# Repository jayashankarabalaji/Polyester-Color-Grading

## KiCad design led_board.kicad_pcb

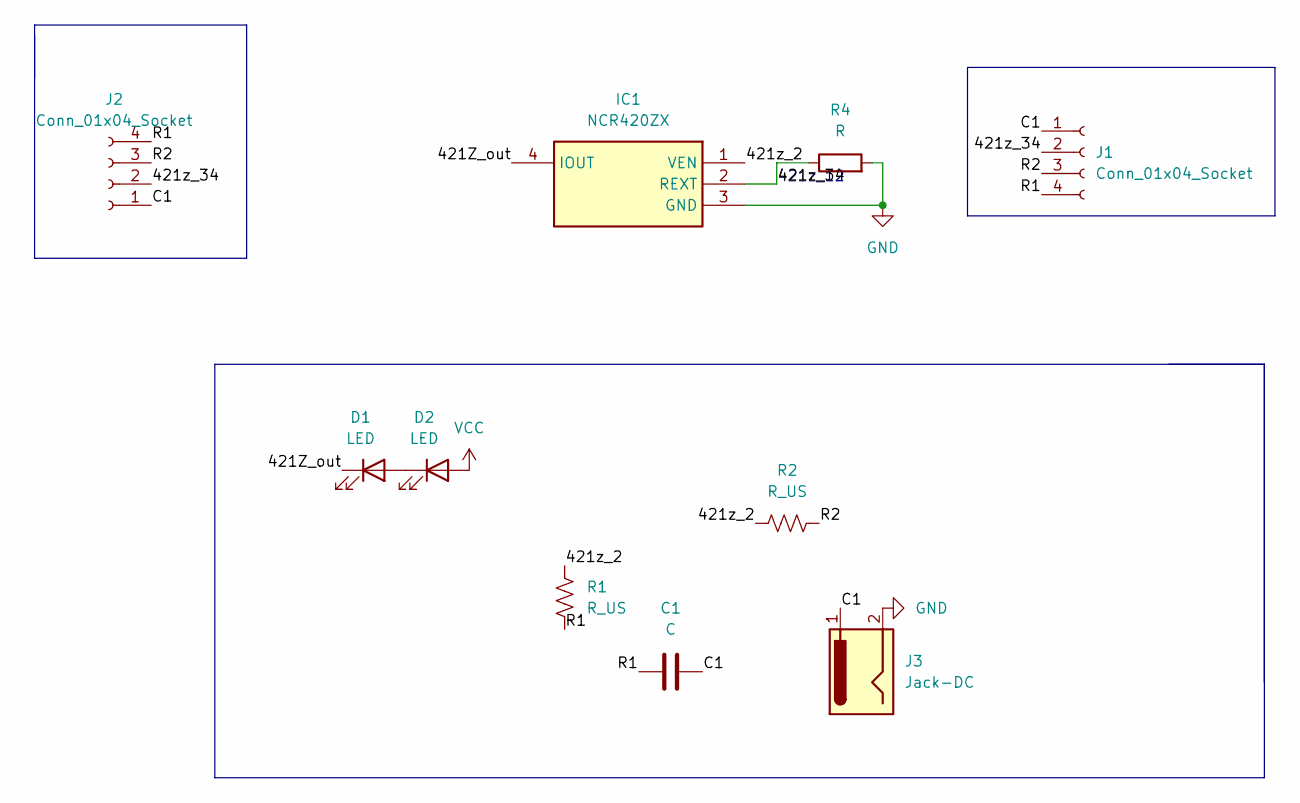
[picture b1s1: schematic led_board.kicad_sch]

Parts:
C1: C; C_0603_1608Metric
D1, D2: LED; LED_0201_0603Metric
IC1: NCR420ZX; SOT230P700X180-4N; Mouser Part Number 771-NCR420ZX
J1, J2: Conn_01x04_Socket; PinSocket_1x04_P1.00mm_Vertical
J3: Jack-DC; PinHeader_1x02_P1.00mm_Horizontal
R1, R2: R_US; R_0603_1608Metric
R4: R; LED_0201_0603Metric

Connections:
/421Z_out: D1.1 (K), IC1.4 (IOUT)
/421z_2: IC1.1 (VEN), R1.1, R2.2
/421z_34: IC1.2 (REXT), J1.2, J2.2, R4.1
/C1: C1.2, J1.1, J2.1, J3.1
/R1: C1.1, J1.4, J2.4, R1.2
/R2: J1.3, J2.3, R2.1
GND: IC1.3 (GND), J3.2, R4.2
unnamed: D1.2 (A), D2.1 (K)
VCC: D2.2 (A)

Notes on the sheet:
421z_12

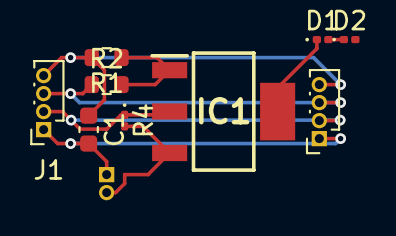
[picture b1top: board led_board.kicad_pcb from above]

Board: 2 copper layers, 10 parts (1 on the bottom side), 8 nets.

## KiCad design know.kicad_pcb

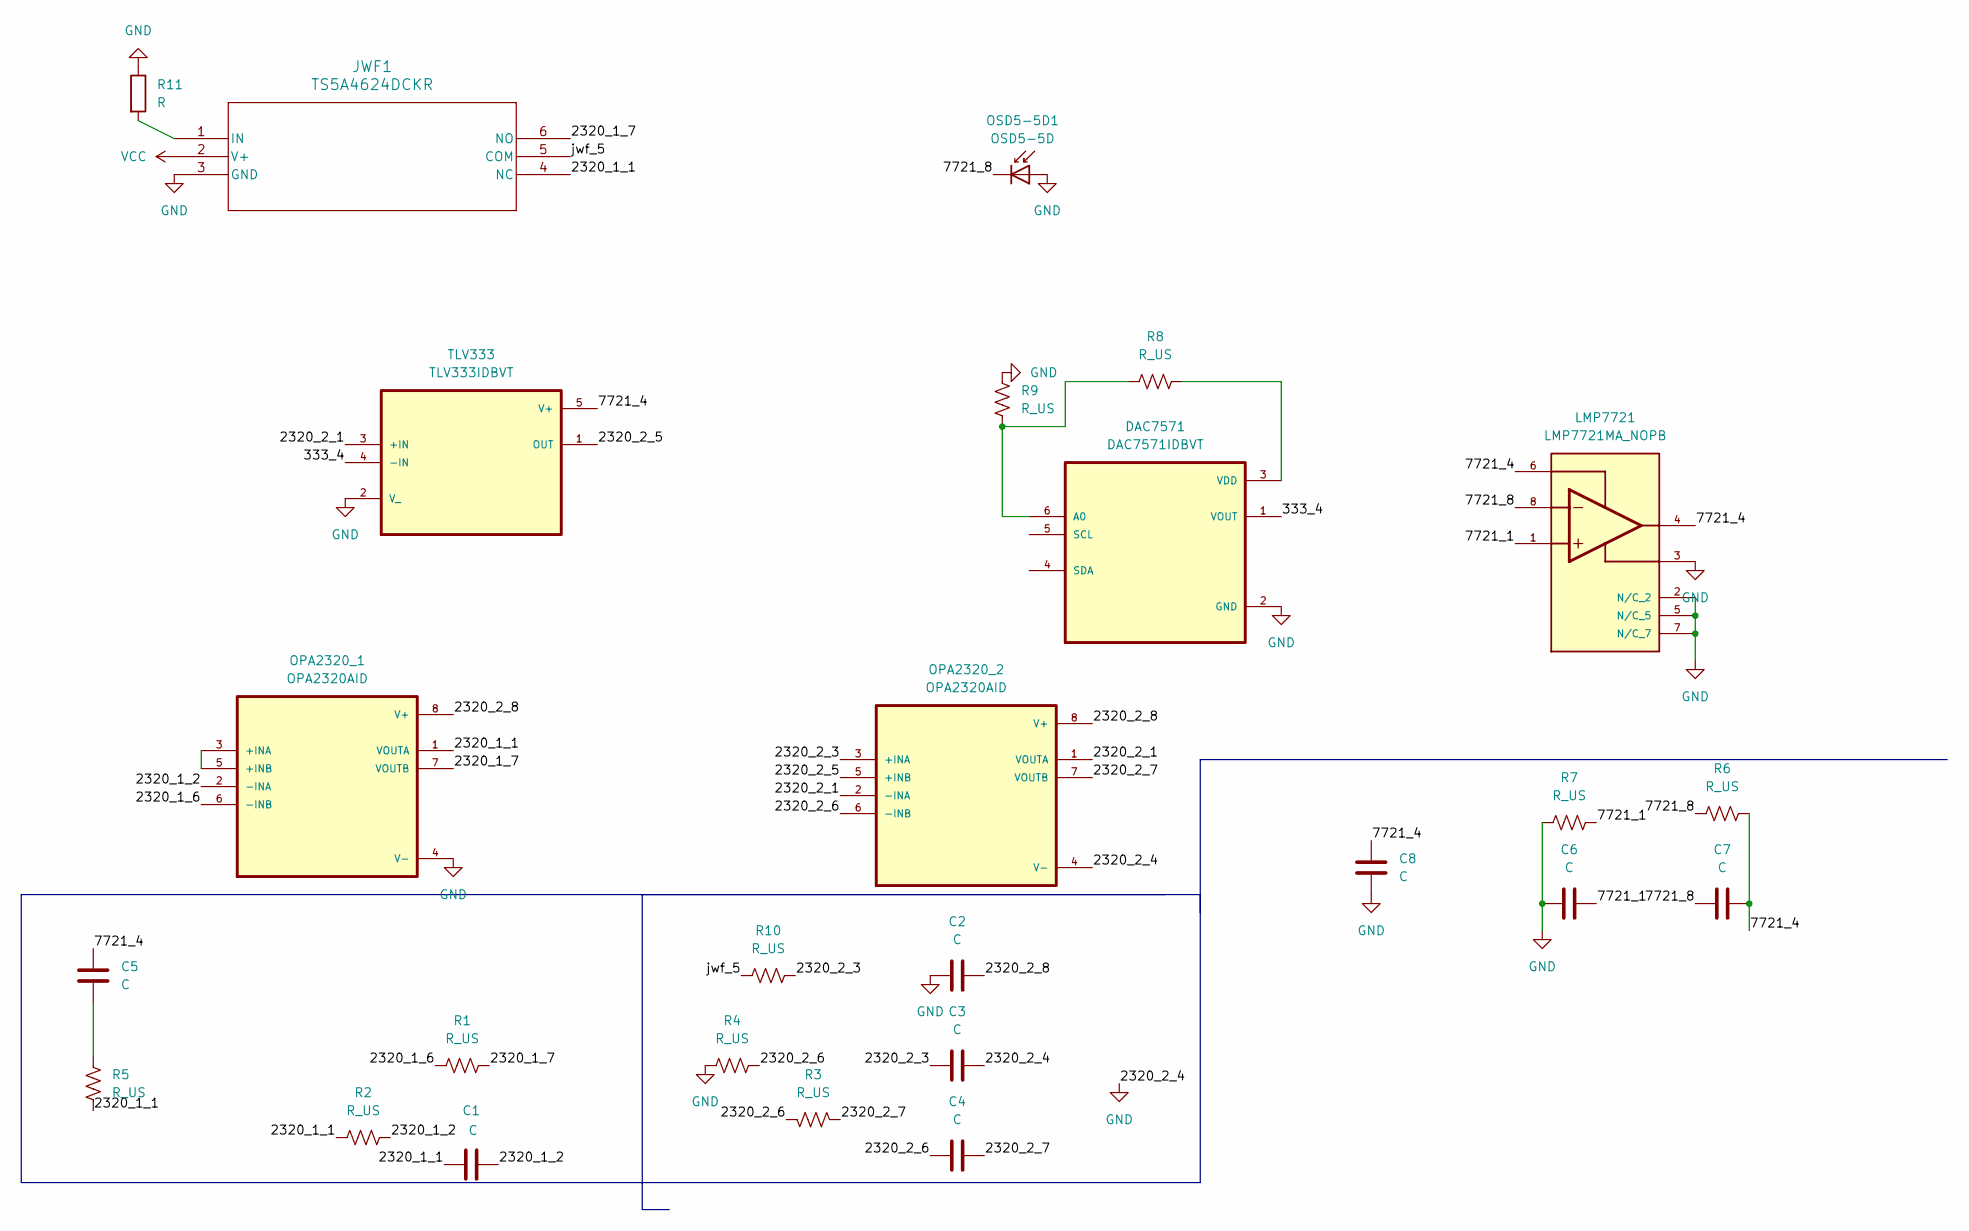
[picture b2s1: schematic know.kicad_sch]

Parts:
C1, C2, C3, C4, C5, C6, C7, C8: C; C_0603_1608Metric
DAC7571: DAC7571IDBVT; SOT95P280X145-6N
JWF1: TS5A4624DCKR; DCK6
LMP7721: LMP7721MA_NOPB; SOIC127P599X175-8N; PARTREV E
OPA2320_1, OPA2320_2: OPA2320AID; SOIC127P599X175-8N
OSD5-5D1: OSD5-5D; TO-5-2
R1, R2, R3, R4, R5, R6, R7, R8, R9, R10: R_US; R_0603_1608Metric
R11: R; R_0201_0603Metric
TLV333: TLV333IDBVT; SOT95P280X145-5N

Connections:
/333_4: DAC7571.1 (VOUT), TLV333.4 (-IN)
/2320_1_1: C1.1, JWF1.4 (NC), OPA2320_1.1 (VOUTA), R2.2, R5.2
/2320_1_2: C1.2, OPA2320_1.2 (-INA), R2.1
/2320_1_6: OPA2320_1.6 (-INB), R1.1
/2320_1_7: JWF1.6 (NO), OPA2320_1.7 (VOUTB), R1.2
/2320_2_1: OPA2320_2.1 (VOUTA), OPA2320_2.2 (-INA), TLV333.3 (+IN)
/2320_2_3: C3.1, OPA2320_2.3 (+INA), R10.2
/2320_2_5: OPA2320_2.5 (+INB), TLV333.1 (OUT)
/2320_2_6: C4.1, OPA2320_2.6 (-INB), R3.1, R4.2
/2320_2_7: C4.2, OPA2320_2.7 (VOUTB), R3.2
/2320_2_8: C2.2, OPA2320_1.8 (V+), OPA2320_2.8 (V+)
/7721_1: C6.2, LMP7721.1, R7.2
/7721_4: C5.1, C7.2, C8.1, LMP7721.4, LMP7721.6, R6.2, TLV333.5 (V+)
/<NO NET>: C7.1, LMP7721.8, OSD5-5D1.1 (K), R6.1
/jwf_5: JWF1.5 (COM), R10.1
GND: C2.1, C3.2, C6.1, C8.2, DAC7571.2 (GND), JWF1.3 (GND), LMP7721.2 (N/C_2), LMP7721.3, LMP7721.5 (N/C_5), LMP7721.7 (N/C_7), OPA2320_1.4 (V-), OPA2320_2.4 (V-), OSD5-5D1.2 (A), R4.1, R7.1, R9.1, R11.1, TLV333.2 (V_)
unnamed: C5.2, R5.1
unnamed: DAC7571.6 (A0), R8.1, R9.2
unnamed: DAC7571.3 (VDD), R8.2
unnamed: JWF1.1 (IN), R11.2
unnamed: OPA2320_1.3 (+INA), OPA2320_1.5 (+INB)
VCC: JWF1.2 (V+)

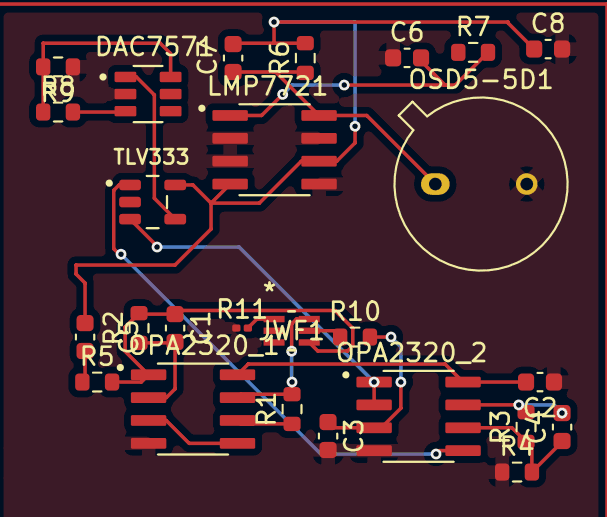
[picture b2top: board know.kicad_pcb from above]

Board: 2 copper layers, 26 parts (0 on the bottom side), 21 nets.
